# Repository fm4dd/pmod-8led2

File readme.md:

## 8LED2 PMOD

### Description

This PMOD provides 8x dual-color LED display output to FPGA designs via two double row PMODs.
It is possible to install either type of dual-color LEDs: "common cathode" or "common anode". The default is "common cathode", which allows for working with normal logic. With normal logic, setting the output "HIGH" lights up the LED. If "common anode" LEDs are installed, JP1 must separate GND, and close the connection to + 3.3V. Common anode uses inverted logic, The LEDs light up when the output is set "LOW".
[fpga.fm4dd.com](http://fpga.fm4dd.com/)

### Schematic

### PCB Gerber

[8LED2 PMOD Gerber V1.0](20200206-8led2-gerber-v10.zip)

### Pin Assignments

#### IceBreaker v1.0

 J1# |  Label | Description   | PMOD1A
-----|--------|---------------|-------
1    |  D1    | LED D1 green  | 4
2    |  D2    | LED D2 green  | 2
3    |  D3    | LED D3 green  | 47
4    |  D4    | LED D4 green  | 45
7    |  D5    | LED D5 green  | 3
8    |  D6    | LED D6 green  | 48
9    |  D7    | LED D7 green  | 46
10   |  D8    | LED D8 green  | 44

 J2# |  Label | Description   | PMOD1B
-----|--------|---------------|-------
1    |  D1    | LED D1 red    | 43
2    |  D2    | LED D2 red    | 38
3    |  D3    | LED D3 red    | 34
4    |  D4    | LED D4 red    | 31
7    |  D5    | LED D5 red    | 42
8    |  D6    | LED D6 red    | 36
9    |  D7    | LED D7 red    | 32
10   |  D8    | LED D8 red    | 28

#### DE0-Nano-SoC

The connection to Intels DE0-Nano-SoC is made through the pmod2nano adapter.

 J1# |  Label | Description   | GPIO0A | GPIO1A
-----|--------|---------------|--------|--------
1    |  D1    | LED D1 green  | PIN_AF8|PIN_AH27
2    |  D2    | LED D2 green  | PIN_AB4|PIN_AH24
3    |  D3    | LED D3 green  | PIN_Y4 |PIN_AE22
4    |  D4    | LED D4 green  | PIN_U11|PIN_AG20
7    |  D5    | LED D5 green  | PIN_W12|PIN_AA15
8    |  D6    | LED D6 green  | PIN_Y8 |PIN_AG26
9    |  D7    | LED D7 green  | PIN_W8 |PIN_AF23
10   |  D8    | LED D8 green  | PIN_Y5 |PIN_AF21

 J2# |  Label | Description   | GPIO0B | GPIO1B
-----|--------|---------------|--------|--------
1    |  D1    | LED D1 red    | PIN_AG6| PIN_AG23
2    |  D2    | LED D2 red    | PIN_AE4| PIN_AF18
3    |  D3    | LED D3 red    | PIN_T11| PIN_AE20
4    |  D4    | LED D4 red    | PIN_AF6| PIN_AD20
7    |  D5    | LED D5 red    | PIN_AF4| PIN_AH23
8    |  D6    | LED D6 red    | PIN_AF5| PIN_AE19
9    |  D7    | LED D7 red    | PIN_T13| PIN_AD19
10   |  D8    | LED D8 red    | PIN_AE7| PIN_AE24

### Example Code

#### Verilog

Verilog test program pmod8led2_1.v (top-level):
```
// -------------------------------------------------------
// This program tests HW pin assignment, and lights up D1
//--------------------------------------------------------
module pmod8led2_1 (
  output [0:7] pmodledr
);

  reg led;
  assign pmodledr[7] = led;

  always
  begin
    led = 1'b1;  // light up D1
  end
endmodule
```

Verilog test program pmod8led2_2.v (top-level):
```
// -------------------------------------------------------
// This program is a binary counter, displayed on the pmod
// LED D2-8 green color. The 1Hz clock pulse is on D1 red.
// 12MHz clock: set breakpoint at 23'd5999999 (icebreaker)
// 50MHz clock: set breakpoint at 25'd24999999 (de0-nano)
//--------------------------------------------------------
module pmod8led2_2 (
  input clk,
  output reg [0:7] pmodledg,
  output reg [0:7] pmodledr
);

  reg clk_1hz = 1'b0;
  reg [22:0] count = 23'd0;
  reg [6:0] lednum = 7'd0;
  assign [1:7] pmodledg = lednum;
  assign [1:7] pmodledr = 7'b0000000;
  assign pmodledr[0] = clk_1hz;

  always @(posedge clk)
  begin
    count   <= count + 1;
    if(count == 23'd5999999)
    begin
      count   <= 0;
      clk_1hz <= ~clk_1hz;
      lednum  <= lednum + 1;
    end
  end
endmodule
```

#### VHDL

The Verilog example pmod8led2_2.v converted to VHDL as pmod8led2_3.vhd:

```
-- -------------------------------------------------------
-- This program is a binary counter, displayed on the pmod
-- LED D1-7 green color. The 1Hz clock pulse is on D8 red.
-- 12MHz clock: set breakpoint at 23'd5999999 (icebreaker)
-- 50MHz clock: set breakpoint at 25'd24999999 (de0-nano)
-- 25MHz clock: set breakpoint at 24'd12499999 (ulx3s)
-- -------------------------------------------------------
library ieee;
use ieee.std_logic_1164.all;
use ieee.numeric_std.all;

entity pmod_8led2_3 is
port (
       clk: in STD_LOGIC;
  pmodledg: out STD_LOGIC_VECTOR(0 to 7) := "00000000";
  pmodledr: out STD_LOGIC_VECTOR(0 to 7) := "00000000"
);
end pmod_8led2_3;

architecture arch of pmod_8led2_3 is
  signal clk_1hz: STD_LOGIC := '0';

  begin
    counter_p: process( clk, clk_1hz )
    variable count: INTEGER := 0;
    variable lednum: STD_LOGIC_VECTOR(6 downto 0) := "0000000";
    begin
      if( rising_edge(clk) ) then
             count := count + 1;
        if( count = 5999999 ) then
               count := 0;
               clk_1hz <= NOT clk_1hz;
               lednum  := std_logic_vector( unsigned(lednum) + 1);
        end if;
           end if;

    pmodledr <= (0 => clk_1hz, others => '0');
    pmodledg(0) <= '0';
    pmodledg(1) <= lednum(6);
    pmodledg(2) <= lednum(5);
    pmodledg(3) <= lednum(4);
    pmodledg(4) <= lednum(3);
    pmodledg(5) <= lednum(2);
    pmodledg(6) <= lednum(1);
    pmodledg(7) <= lednum(0);

  end process counter_p;
end arch;
```

8LED2 PMOD on a DE0-Nano-SoC board

8LED2 PMOD on a ULX3S Lattice ECP 85K board

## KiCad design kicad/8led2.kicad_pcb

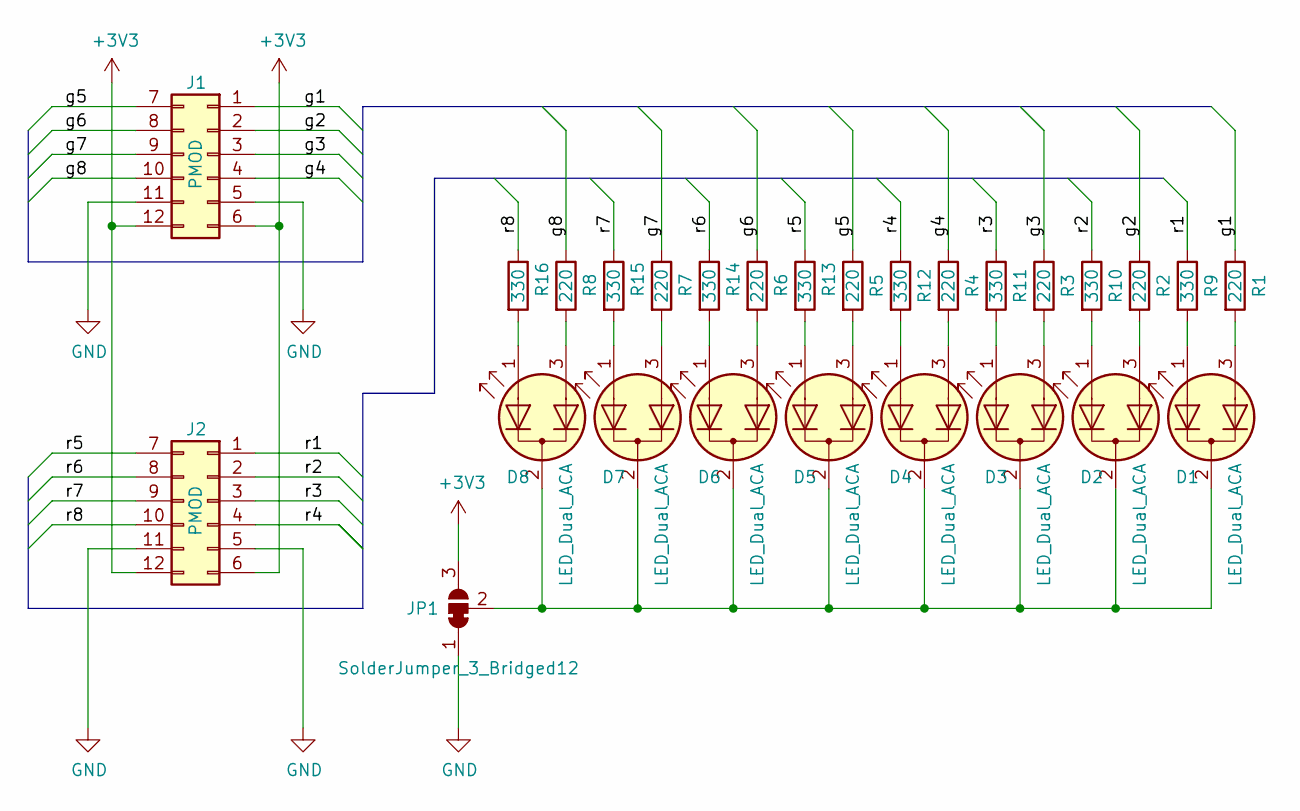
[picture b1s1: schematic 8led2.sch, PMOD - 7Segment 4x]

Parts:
D1, D2, D3, D4, D5, D6, D7, D8: LED_Dual_ACA; LED_D3.0mm-3
J1, J2: PMOD; PMODHeader_2x06_P2.54mm_Horizontal
JP1: SolderJumper_3_Bridged12; SolderJumper-3_P1.3mm_Bridged2Bar12_Pad1.0x1.5mm
R1, R2, R3, R4, R5, R6, R7, R8: 220; R_Axial_DIN0204_L3.6mm_D1.6mm_P5.08mm_Horizontal
R9, R10, R11, R12, R13, R14, R15, R16: 330; R_Axial_DIN0204_L3.6mm_D1.6mm_P5.08mm_Horizontal

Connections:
+3V3: J1.6, J1.12, J2.6, J2.12, JP1.3 (B)
/g1: J1.1, R1.1
/g2: J1.2, R2.1
/g3: J1.3, R3.1
/g4: J1.4, R4.1
/g5: J1.7, R5.1
/g6: J1.8, R6.1
/g7: J1.9, R7.1
/g8: J1.10, R8.1
/r1: J2.1, R9.1
/r2: J2.2, R10.1
/r3: J2.3, R11.1
/r4: J2.4, R12.1
/r5: J2.7, R13.1
/r6: J2.8, R14.1
/r7: J2.9, R15.1
/r8: J2.10, R16.1
GND: J1.5, J1.11, J2.5, J2.11, JP1.1 (A)
unnamed: D1.1 (A1), R9.2
unnamed: D1.2 (K), D2.2 (K), D3.2 (K), D4.2 (K), D5.2 (K), D6.2 (K), D7.2 (K), D8.2 (K), JP1.2 (C)
unnamed: D1.3 (A2), R1.2
unnamed: D2.1 (A1), R10.2
unnamed: D2.3 (A2), R2.2
unnamed: D3.1 (A1), R11.2
unnamed: D3.3 (A2), R3.2
unnamed: D4.1 (A1), R12.2
unnamed: D4.3 (A2), R4.2
unnamed: D5.1 (A1), R13.2
unnamed: D5.3 (A2), R5.2
unnamed: D6.1 (A1), R14.2
unnamed: D6.3 (A2), R6.2
unnamed: D7.1 (A1), R15.2
unnamed: D7.3 (A2), R7.2
unnamed: D8.1 (A1), R16.2
unnamed: D8.3 (A2), R8.2

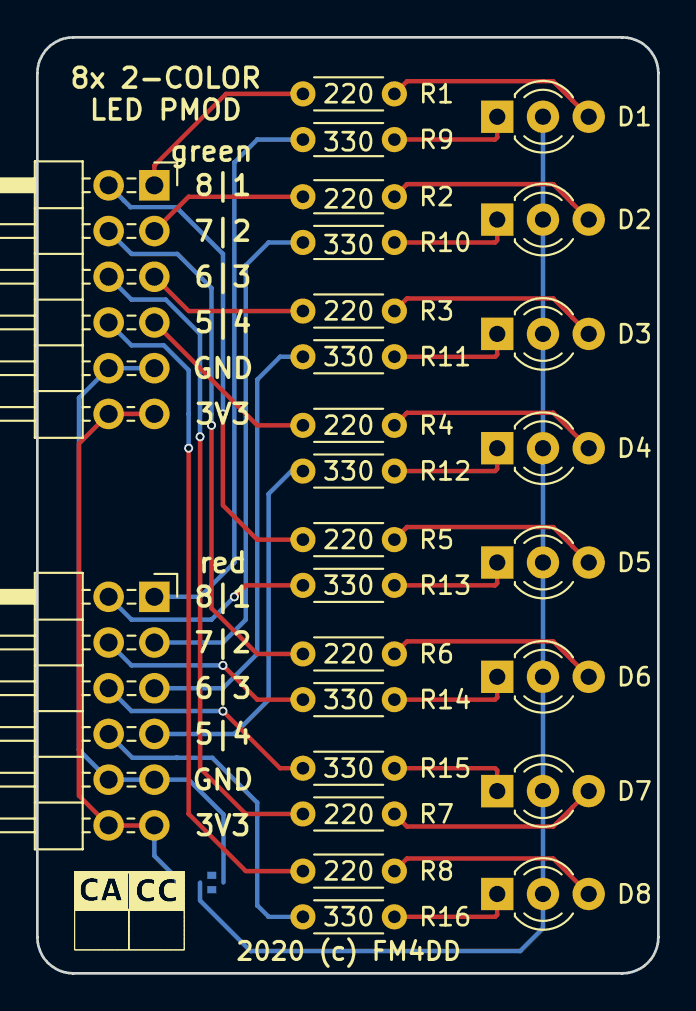
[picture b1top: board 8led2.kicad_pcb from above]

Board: 2 copper layers, 34.5 x 52.0 mm, 28 parts (1 on the bottom side), 35 nets.

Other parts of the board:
7seg-type-display: 7seg-type-display

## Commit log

2020-03-20 add fpga url
2020-04-02 fix pin assignment and add VHDL example
2020-04-04 update schema, add BOM
2020-04-19 add Verilog/VHDL demo code
2020-04-23 fix git lang discovery
2020-11-26 Add ULX3S example
2020-11-30 add ULX3S VHDL example
2020-12-02 Update VHDL example

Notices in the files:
kicad/8led2.kicad_pcb:
License: CC-BY-SA 4.0
CC-BY-SA
